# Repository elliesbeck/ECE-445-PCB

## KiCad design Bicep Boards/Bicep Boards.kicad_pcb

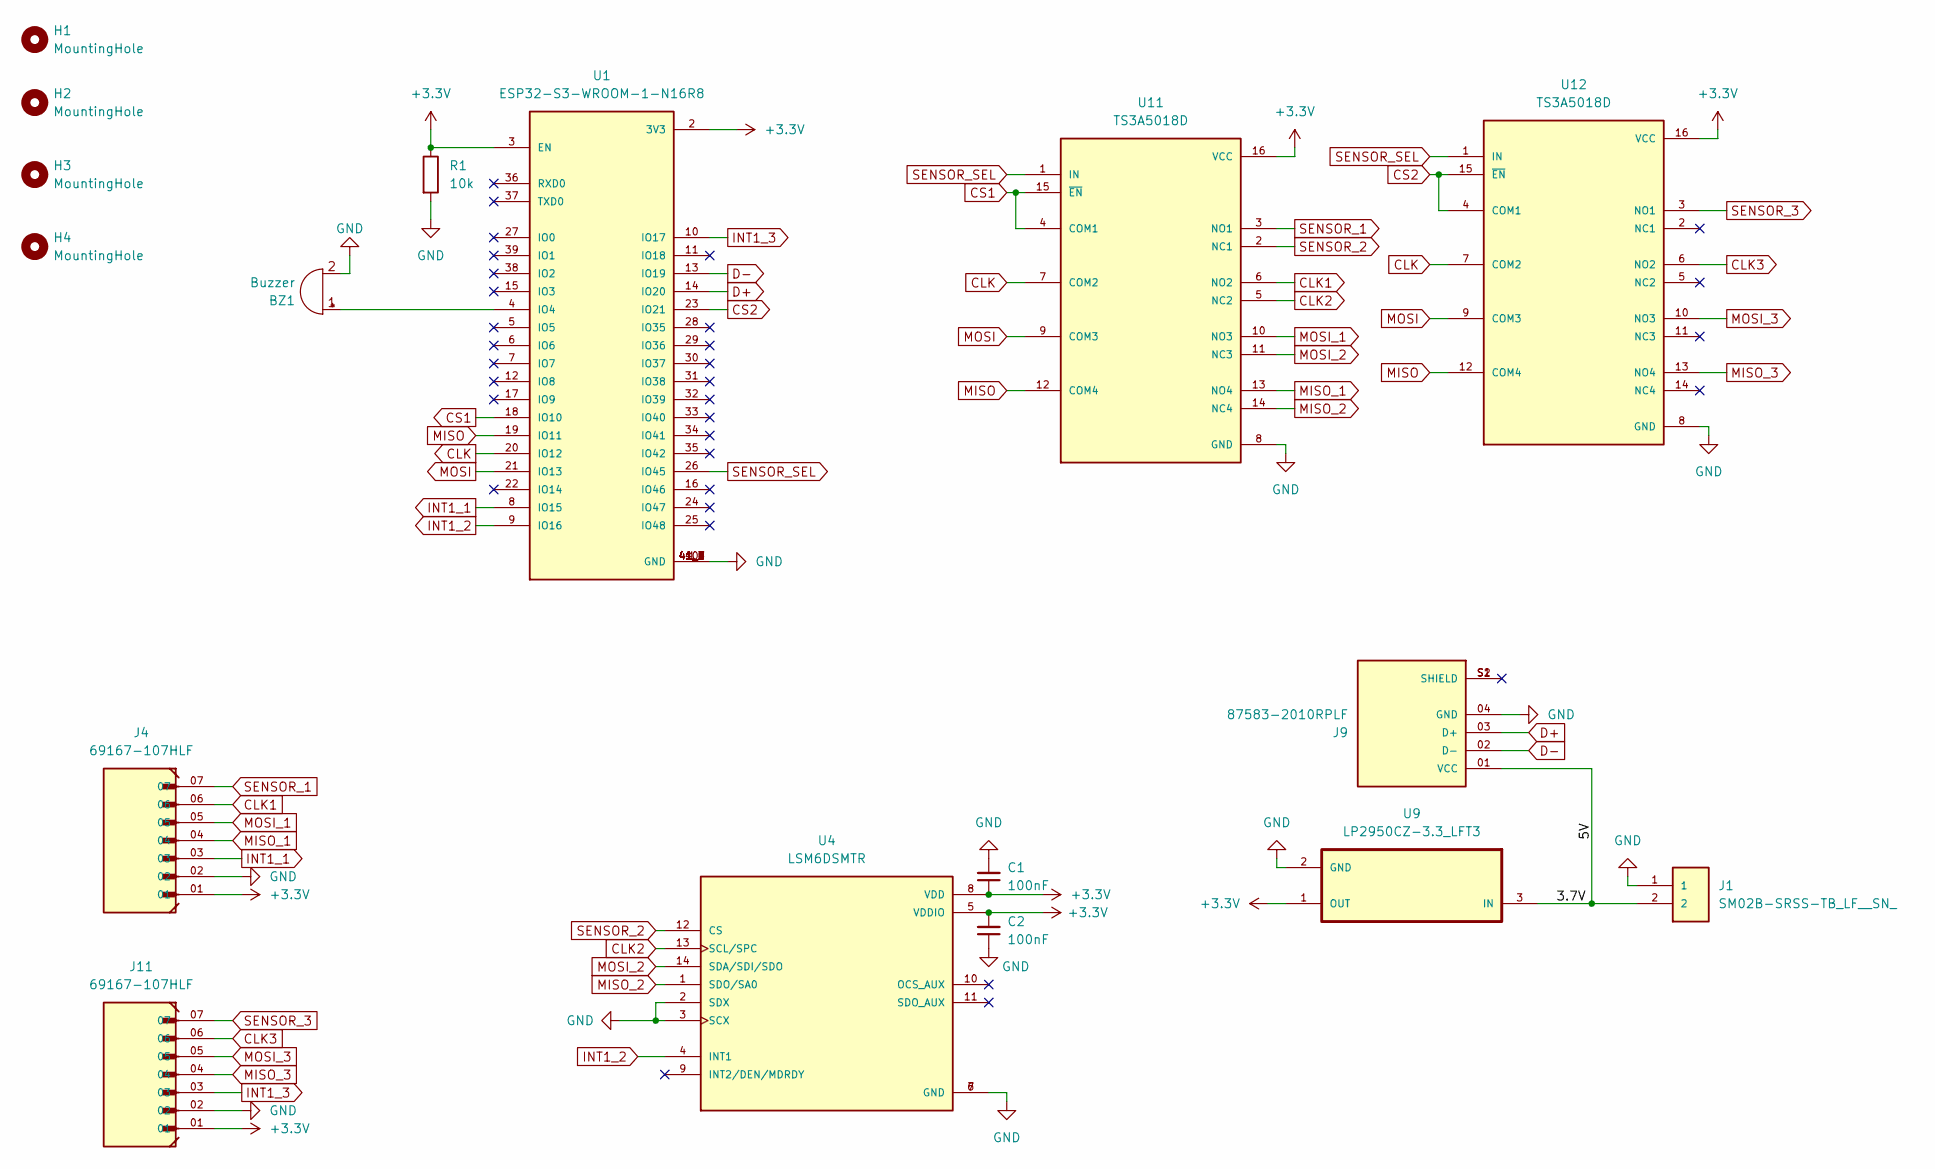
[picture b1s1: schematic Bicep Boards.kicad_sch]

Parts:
BZ1: Buzzer; AC-903-D-1P
C1, C2: 100nF; CAPC2012X135N
H1, H2, H3, H4: MountingHole; MountingHole_2mm
J1: SM02B-SRSS-TB_LF__SN_
J4, J11: 69167-107HLF; AMPHENOL_69167-107HLF; PARTREV W
J9: 87583-2010RPLF; AMPHENOL_87583-2010RPLF; PARTREV AD
R1: 10k; RESC2012X65N
U1: ESP32-S3-WROOM-1-N16R8; XCVR_ESP32-S3-WROOM-1-N16R8
U4: LSM6DSMTR; PQFN50P300X250X86-14N; PARTREV Rev 7
U9: LP2950CZ-3.3_LFT3; TO92127P521H735-3
U11, U12: TS3A5018D; SOIC127P600X175-16N; PARTREV H

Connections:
+3.3V: C1.1, C2.2, J4.01, J11.01, R1.1, U1.2 (3V3), U1.3 (EN), U4.5 (VDDIO), U4.8 (VDD), U9.1 (OUT), U11.16 (VCC), U12.16 (VCC)
/3.7V: J1.2, J9.01 (VCC), U9.3 (IN)
CLK: U1.20 (IO12), U11.7 (COM2), U12.7 (COM2)
CLK1: J4.06, U11.6 (NO2)
CLK2: U4.13 (SCL/SPC), U11.5 (NC2)
CLK3: J11.06, U12.6 (NO2)
CS1: U1.18 (IO10), U11.4 (COM1), U11.15 (~EN)
CS2: U1.23 (IO21), U12.4 (COM1), U12.15 (~EN)
D+: J9.03 (D+), U1.14 (IO20)
D-: J9.02 (D-), U1.13 (IO19)
GND: BZ1.2 (-), C1.2, C2.1, J1.1, J4.02, J9.04 (GND), J11.02, R1.2, U1.1 (GND), U1.40 (GND), U1.41_1 (GND), U1.41_2 (GND), U1.41_3 (GND), U1.41_4 (GND), U1.41_5 (GND), U1.41_6 (GND), U1.41_7 (GND), U1.41_8 (GND), U1.41_9 (GND), U4.2 (SDX), U4.3 (SCX), U4.6 (GND), U4.7 (GND), U9.2 (GND), U11.8 (GND), U12.8 (GND)
INT1_1: J4.03, U1.8 (IO15)
INT1_2: U1.9 (IO16), U4.4 (INT1)
INT1_3: J11.03, U1.10 (IO17)
MISO: U1.19 (IO11), U11.12 (COM4), U12.12 (COM4)
MISO_1: J4.04, U11.13 (NO4)
MISO_2: U4.1 (SDO/SA0), U11.14 (NC4)
MISO_3: J11.04, U12.13 (NO4)
MOSI: U1.21 (IO13), U11.9 (COM3), U12.9 (COM3)
MOSI_1: J4.05, U11.10 (NO3)
MOSI_2: U4.14 (SDA/SDI/SDO), U11.11 (NC3)
MOSI_3: J11.05, U12.10 (NO3)
unnamed: BZ1.1 (+), U1.4 (IO4)
SENSOR_1: J4.07, U11.3 (NO1)
SENSOR_2: U4.12 (CS), U11.2 (NC1)
SENSOR_3: J11.07, U12.3 (NO1)
SENSOR_SEL: U1.26 (IO45), U11.1 (IN), U12.1 (IN)

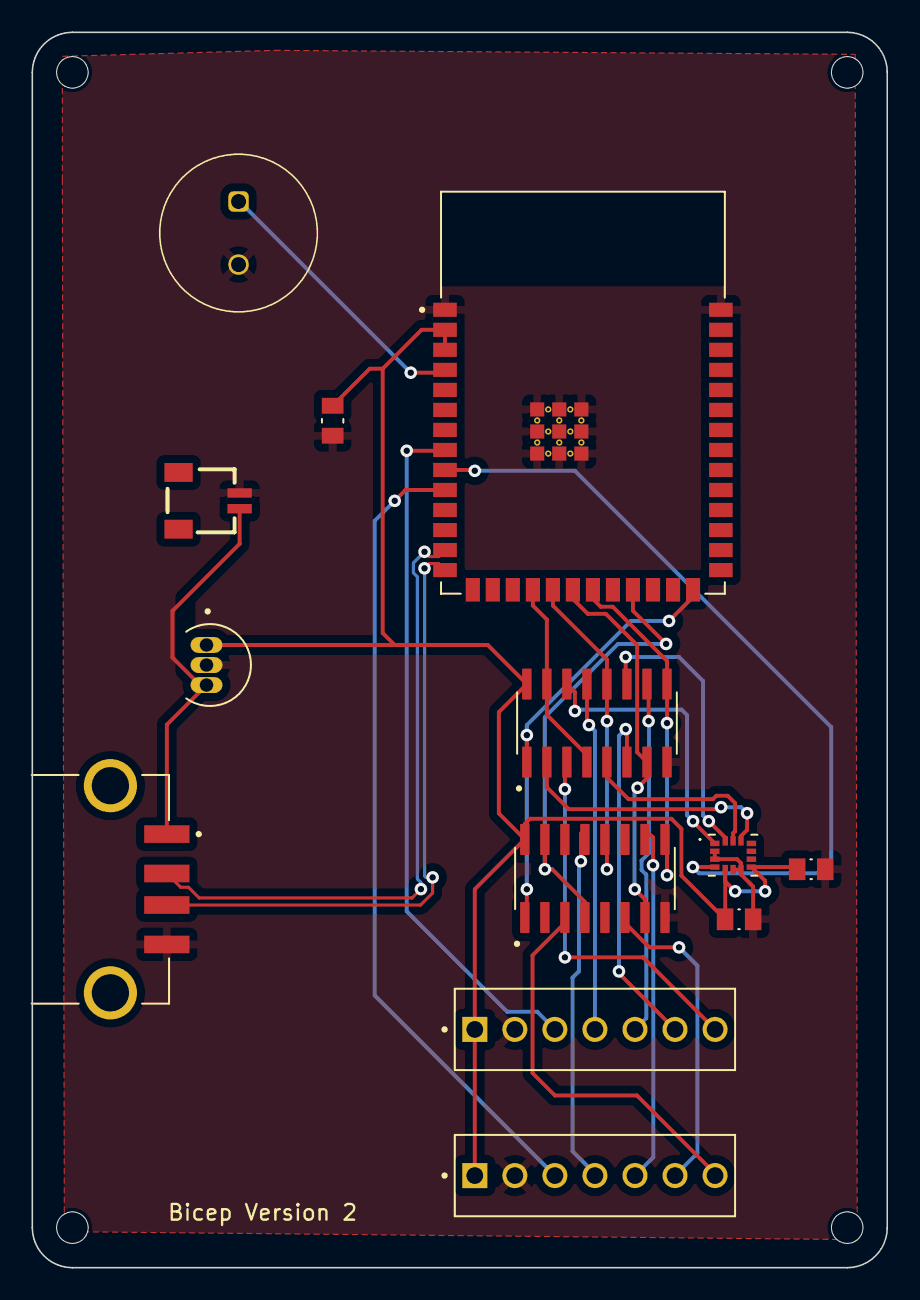
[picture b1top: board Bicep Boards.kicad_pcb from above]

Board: 2 copper layers, 54.2 x 78.4 mm, 17 parts (0 on the bottom side), 27 nets.

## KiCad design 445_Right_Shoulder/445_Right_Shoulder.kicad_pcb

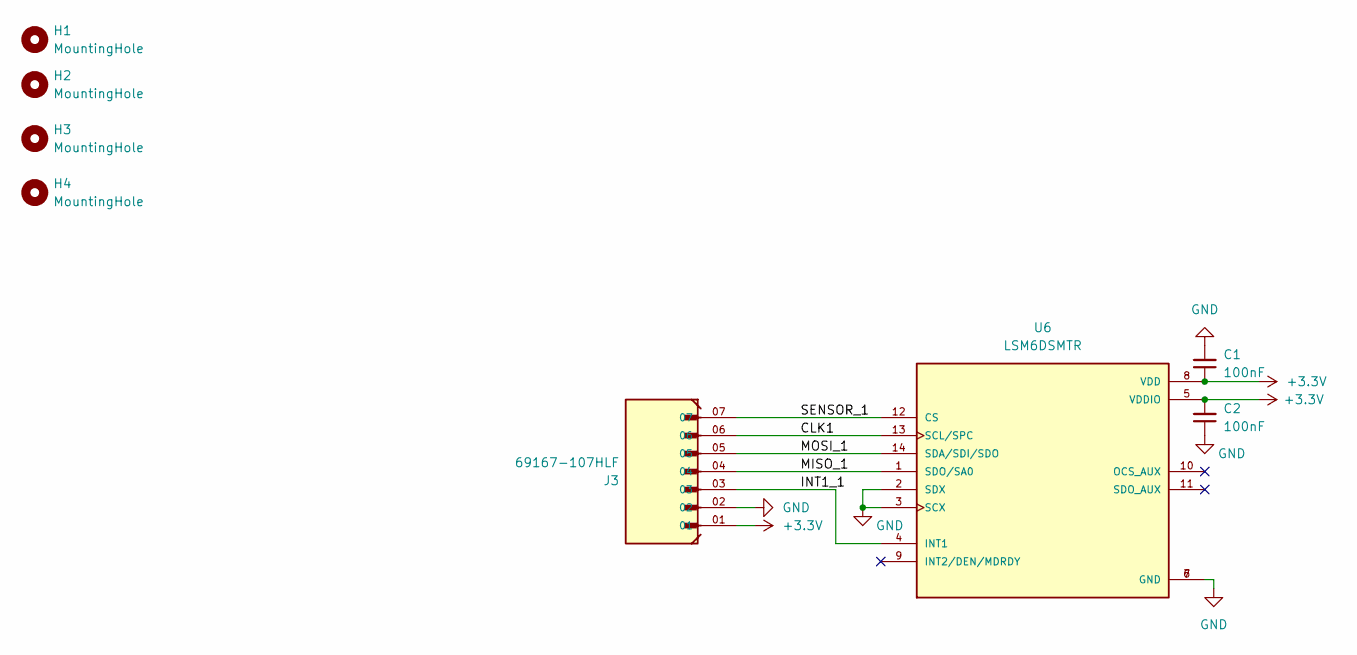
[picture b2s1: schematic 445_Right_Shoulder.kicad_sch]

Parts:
C1, C2: 100nF; CAPC2012X135N
H1, H2, H3, H4: MountingHole; MountingHole_2mm
J3: 69167-107HLF; AMPHENOL_69167-107HLF; PARTREV W
U6: LSM6DSMTR; PQFN50P300X250X86-14N; PARTREV Rev 7

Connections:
+3.3V: C1.1, C2.2, J3.01, U6.5 (VDDIO), U6.8 (VDD)
/CLK1: J3.06, U6.13 (SCL/SPC)
/INT1_1: J3.03, U6.4 (INT1)
/MISO_1: J3.04, U6.1 (SDO/SA0)
/MOSI_1: J3.05, U6.14 (SDA/SDI/SDO)
/SENSOR_1: J3.07, U6.12 (CS)
GND: C1.2, C2.1, J3.02, U6.2 (SDX), U6.3 (SCX), U6.6 (GND), U6.7 (GND)

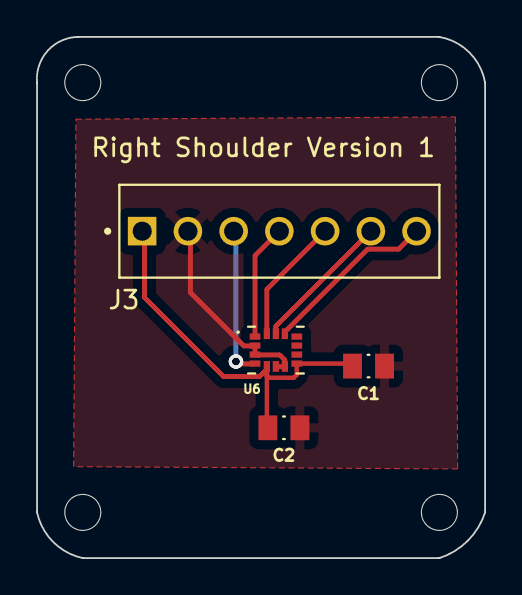
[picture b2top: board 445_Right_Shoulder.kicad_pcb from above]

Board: 2 copper layers, 24.9 x 29.0 mm, 8 parts (0 on the bottom side), 7 nets.

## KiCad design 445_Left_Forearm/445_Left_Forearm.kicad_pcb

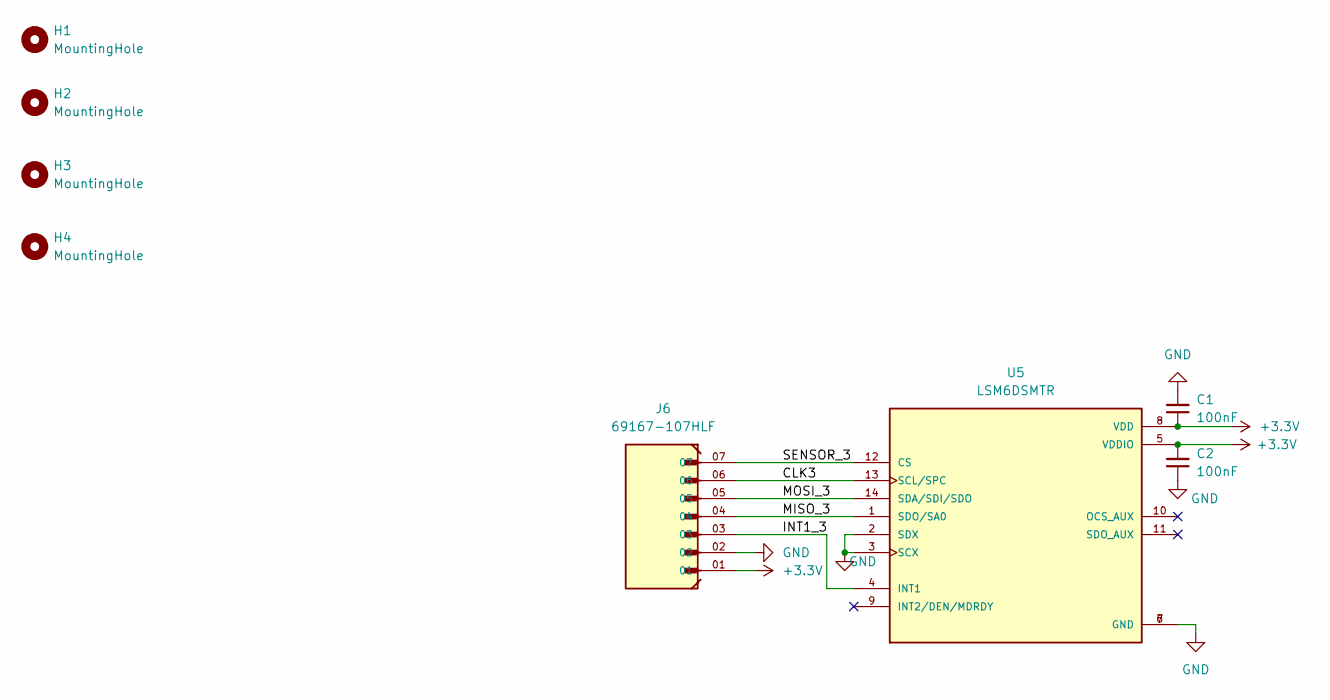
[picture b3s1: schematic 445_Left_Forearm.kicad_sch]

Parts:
C1, C2: 100nF; CAPC2012X135N
H1, H2, H3, H4: MountingHole; MountingHole_2mm
J6: 69167-107HLF; AMPHENOL_69167-107HLF; PARTREV W
U5: LSM6DSMTR; PQFN50P300X250X86-14N; PARTREV Rev 7

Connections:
+3.3V: C1.1, C2.2, J6.01, U5.5 (VDDIO), U5.8 (VDD)
/CLK3: J6.06, U5.13 (SCL/SPC)
/INT1_3: J6.03, U5.4 (INT1)
/MISO_3: J6.04, U5.1 (SDO/SA0)
/MOSI_3: J6.05, U5.14 (SDA/SDI/SDO)
/SENSOR_3: J6.07, U5.12 (CS)
GND: C1.2, C2.1, J6.02, U5.2 (SDX), U5.3 (SCX), U5.6 (GND), U5.7 (GND)

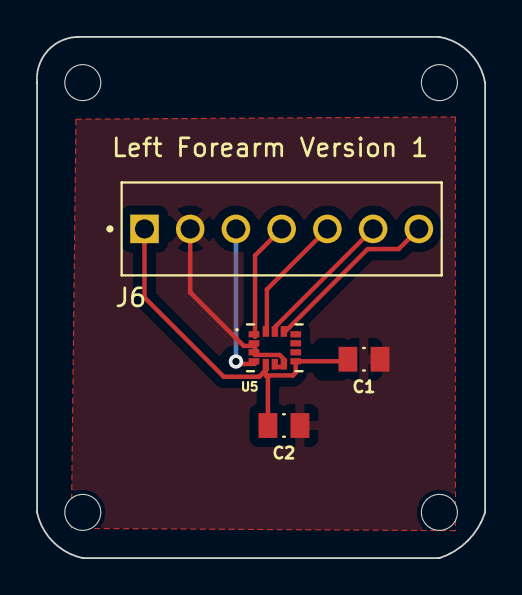
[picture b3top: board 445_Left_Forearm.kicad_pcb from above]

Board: 2 copper layers, 24.9 x 29.0 mm, 8 parts (0 on the bottom side), 7 nets.

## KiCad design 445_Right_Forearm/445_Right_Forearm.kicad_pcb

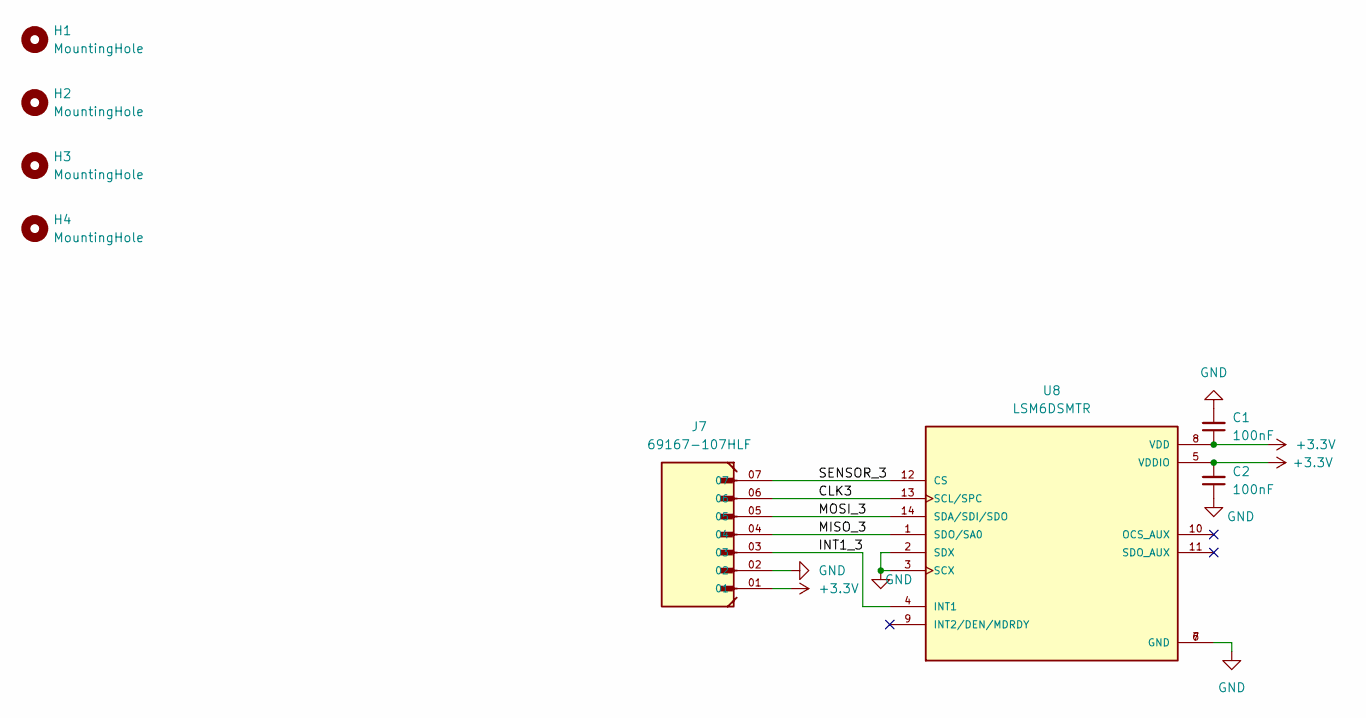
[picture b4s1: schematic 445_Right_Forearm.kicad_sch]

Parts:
C1, C2: 100nF; CAPC2012X135N
H1, H2, H3, H4: MountingHole; MountingHole_2mm
J7: 69167-107HLF; AMPHENOL_69167-107HLF; PARTREV W
U8: LSM6DSMTR; PQFN50P300X250X86-14N; PARTREV Rev 7

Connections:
+3.3V: C1.1, C2.2, J7.01, U8.5 (VDDIO), U8.8 (VDD)
/CLK3: J7.06, U8.13 (SCL/SPC)
/INT1_3: J7.03, U8.4 (INT1)
/MISO_3: J7.04, U8.1 (SDO/SA0)
/MOSI_3: J7.05, U8.14 (SDA/SDI/SDO)
/SENSOR_3: J7.07, U8.12 (CS)
GND: C1.2, C2.1, J7.02, U8.2 (SDX), U8.3 (SCX), U8.6 (GND), U8.7 (GND)

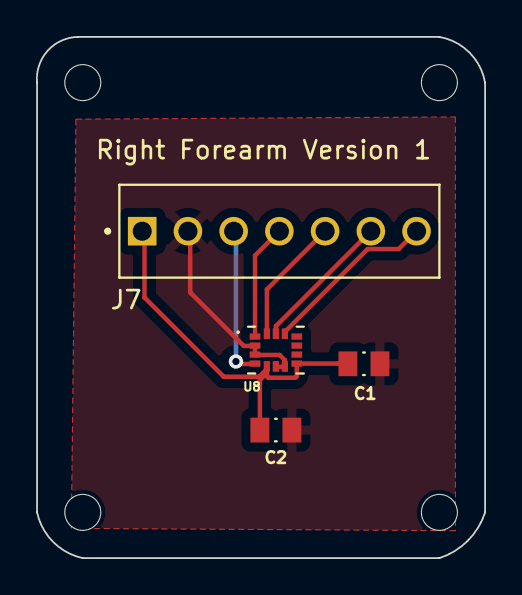
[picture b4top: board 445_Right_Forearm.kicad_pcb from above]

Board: 2 copper layers, 24.9 x 29.0 mm, 8 parts (0 on the bottom side), 7 nets.

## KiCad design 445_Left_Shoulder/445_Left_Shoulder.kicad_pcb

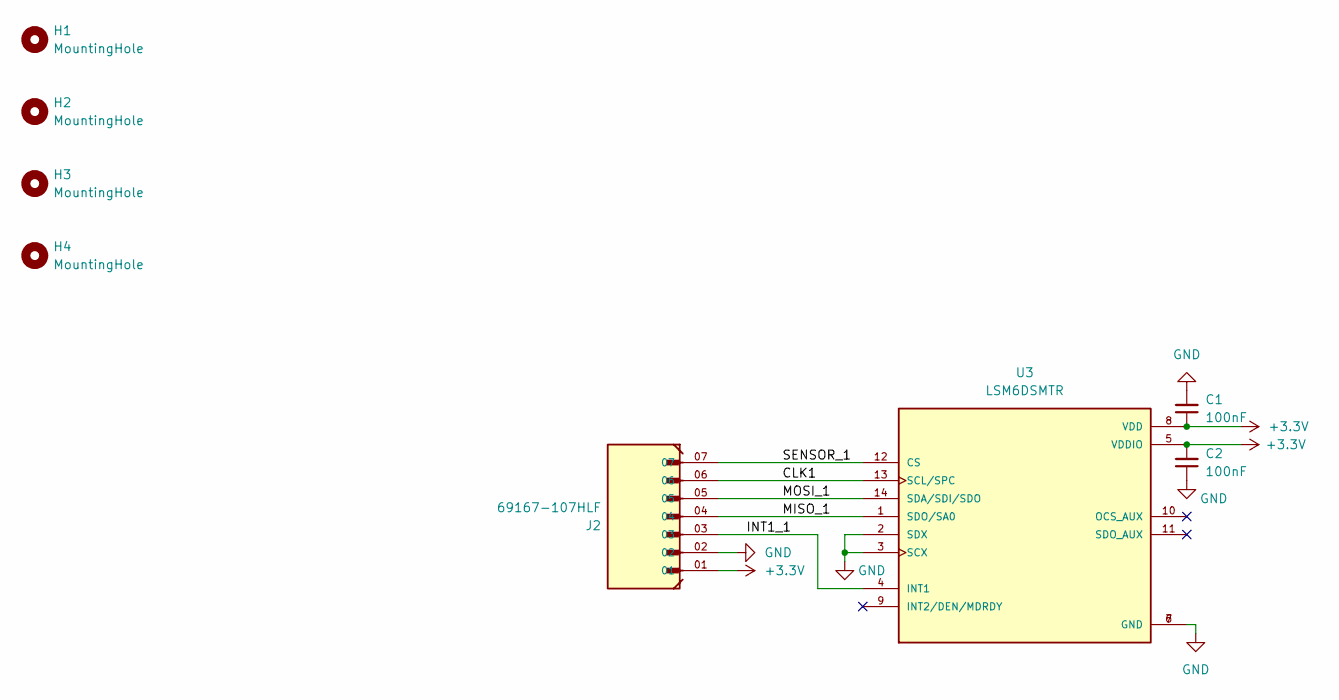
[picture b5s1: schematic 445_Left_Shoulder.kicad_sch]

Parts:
C1, C2: 100nF; CAPC2012X135N
H1, H2, H3, H4: MountingHole; MountingHole_2mm
J2: 69167-107HLF; AMPHENOL_69167-107HLF; PARTREV W
U3: LSM6DSMTR; PQFN50P300X250X86-14N; PARTREV Rev 7

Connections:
+3.3V: C1.1, C2.2, J2.01, U3.5 (VDDIO), U3.8 (VDD)
/CLK1: J2.06, U3.13 (SCL/SPC)
/INT1_1: J2.03, U3.4 (INT1)
/MISO_1: J2.04, U3.1 (SDO/SA0)
/MOSI_1: J2.05, U3.14 (SDA/SDI/SDO)
/SENSOR_1: J2.07, U3.12 (CS)
GND: C1.2, C2.1, J2.02, U3.2 (SDX), U3.3 (SCX), U3.6 (GND), U3.7 (GND)

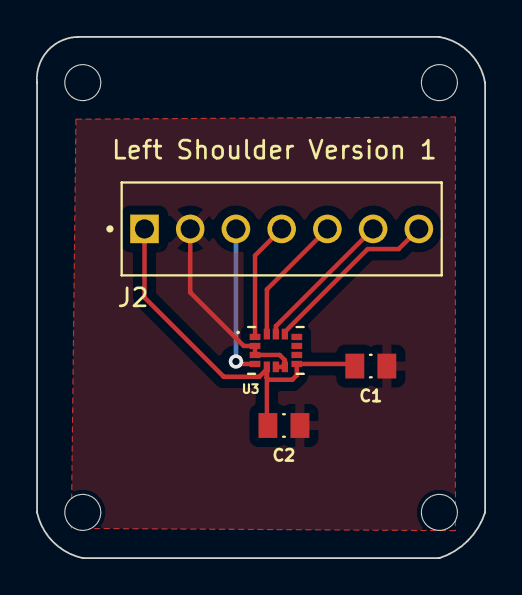
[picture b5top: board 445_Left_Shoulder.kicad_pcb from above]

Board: 2 copper layers, 24.9 x 29.0 mm, 8 parts (0 on the bottom side), 7 nets.

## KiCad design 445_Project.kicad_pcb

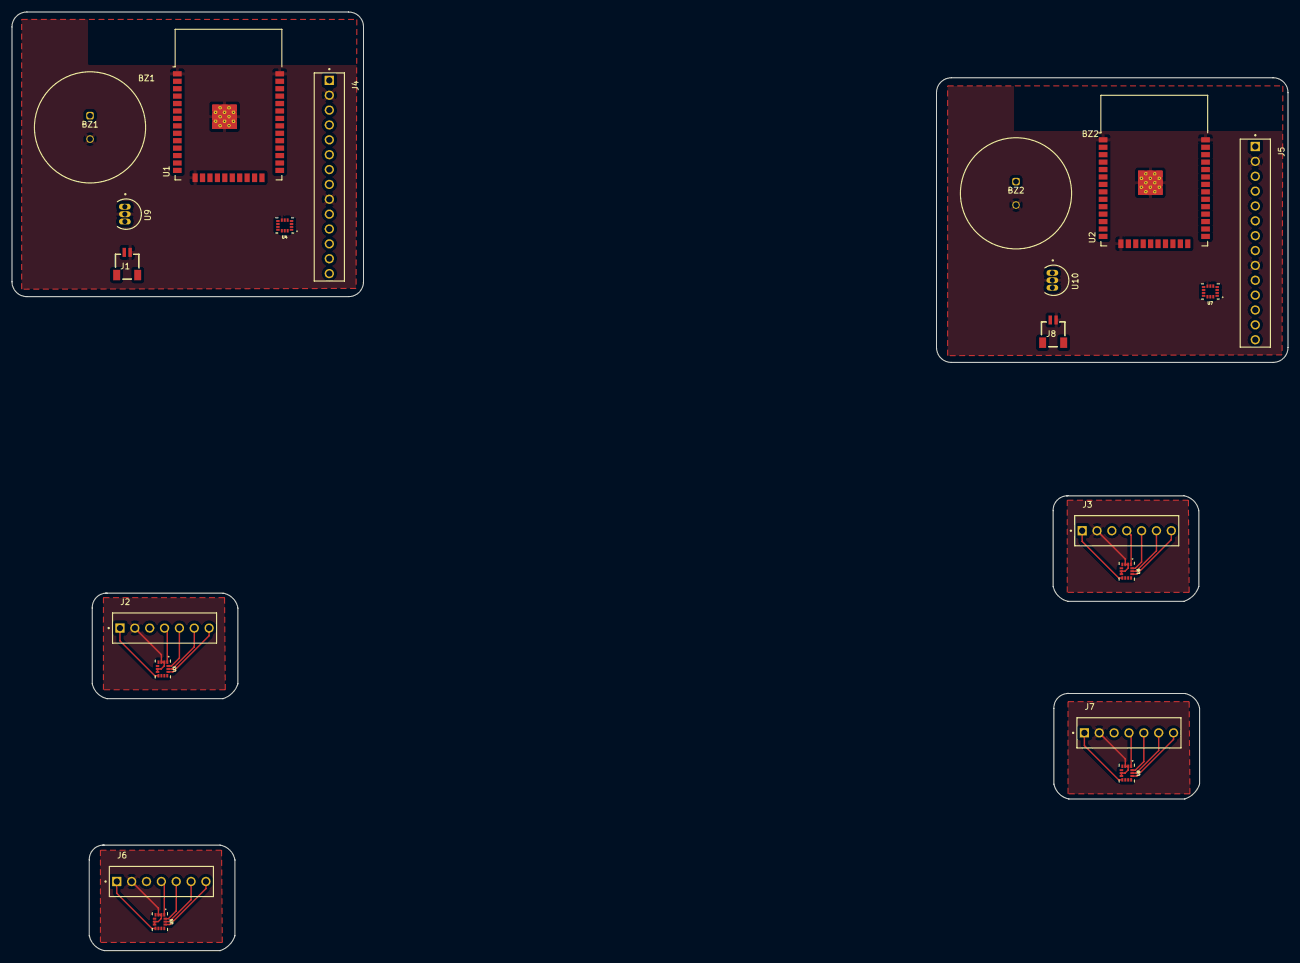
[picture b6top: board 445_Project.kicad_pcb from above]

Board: 2 copper layers, 218.1 x 160.4 mm, 20 parts (0 on the bottom side), 13 nets.

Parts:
BZ1, BZ2: Buzzer; AC-903-D-1P
J1, J8: SM02B-SRSS-TB_LF__SN_
J2, J3, J6, J7: 69167-107HLF; AMPHENOL_69167-107HLF
J4, J5: 69167-114HLF; AMPHENOL_69167-114HLF
U1, U2: ESP32-WROOM-32
U3, U4, U5, U6, U7, U8: LSM6DSMTR; PQFN50P300X250X86-14N
U9, U10: LP2950CZ-3.3_LFT3; TO92127P521H735-3

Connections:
3.3V: U1.2 (VDD), U2.2 (VDD), U9.1 (OUT), U10.1 (OUT)
+3.3V: J2.01, J3.01, J4.01, J4.08, J5.01, J5.08, J6.01, J7.01, U3.8 (VDD), U4.8 (VDD), U5.8 (VDD), U6.8 (VDD), U7.8 (VDD), U8.8 (VDD)
CLK: J2.06, J3.06, J4.06, J4.13, J5.06, J5.13, J6.06, J7.06, U1.30 (IO18), U2.30 (IO18), U3.13 (SCL/SPC), U4.13 (SCL/SPC), U5.13 (SCL/SPC), U6.13 (SCL/SPC), U7.13 (SCL/SPC), U8.13 (SCL/SPC)
CS0: J2.07, J3.07, J4.14, J5.14, U1.29 (IO5), U2.29 (IO5), U3.12 (CS), U6.12 (CS)
CS1: U1.28 (IO17), U2.28 (IO17), U4.12 (CS), U7.12 (CS)
CS2: J4.07, J5.07, J6.07, J7.07, U1.27 (IO16), U2.27 (IO16), U5.12 (CS), U8.12 (CS)
GND: BZ1.2 (-), BZ2.2 (-), J1.2, J2.02, J3.02, J4.02, J4.09, J5.02, J5.09, J6.02, J7.02, J8.2, U1.1 (GND), U1.15 (GND), U1.38 (GND), U1.39 (GND), U2.1 (GND), U2.15 (GND), U2.38 (GND), U2.39 (GND), U3.2 (SDX), U3.3 (SCX), U3.6 (GND), U3.7 (GND), U4.2 (SDX), U4.3 (SCX), U4.6 (GND), U4.7 (GND), U5.2 (SDX), U5.3 (SCX), U5.6 (GND), U5.7 (GND), U6.2 (SDX), U6.3 (SCX), U6.6 (GND), U6.7 (GND), U7.3 (SCX), U7.6 (GND), U7.7 (GND), U8.2 (SDX), U8.3 (SCX), U8.6 (GND), U8.7 (GND), U9.2 (GND), U10.2 (GND)
MISO: J2.04, J3.04, J4.04, J4.11, J5.04, J5.11, J6.04, J7.04, U1.31 (IO19), U2.31 (IO19), U3.1 (SDO/SA0), U4.1 (SDO/SA0), U5.1 (SDO/SA0), U6.1 (SDO/SA0), U7.1 (SDO/SA0), U8.1 (SDO/SA0)
MOSI: J2.05, J3.05, J4.05, J4.12, J5.05, J5.12, J6.05, J7.05, U1.23 (IO15), U2.23 (IO15), U3.14 (SDA/SDI/SDO), U4.14 (SDA/SDI/SDO), U5.14 (SDA/SDI/SDO), U6.14 (SDA/SDI/SDO), U7.14 (SDA/SDI/SDO), U8.14 (SDA/SDI/SDO)
unnamed: BZ1.1 (+), U1.33 (IO21)
unnamed: BZ2.1 (+), U2.33 (IO21)
unnamed: J1.1, U9.3 (IN)
unnamed: J8.1, U10.3 (IN)

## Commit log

2024-03-04 Added filtering caps and int line
2024-03-11 enable signal and analog switches
2024-03-11 replace bicep connector and add int1 connections
2024-03-12 Layout First Draft
2024-03-12 adding buzzer
2024-03-12 Edits 3/12
2024-03-13 D+ and D- as differential pairs
2024-03-30 Version 2
2024-04-01 sensor select pin change and silk added
